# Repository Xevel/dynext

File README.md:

dynext
======

Dynamixel extension board.

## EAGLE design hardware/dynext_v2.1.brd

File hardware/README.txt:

Dynext - universal dynamixel device
===================================

V1.0 - 2014/03/02
- 4 layers
- first manufactured board
- smaller power section
- added voltage ref
- cleaner separation of different voltages, and corresponding return path

v0.2 - unfinished, was too hard to route in 2 layers. The power section was nice though.

v0.1 - unfinished, was too hard to route in 2 layers

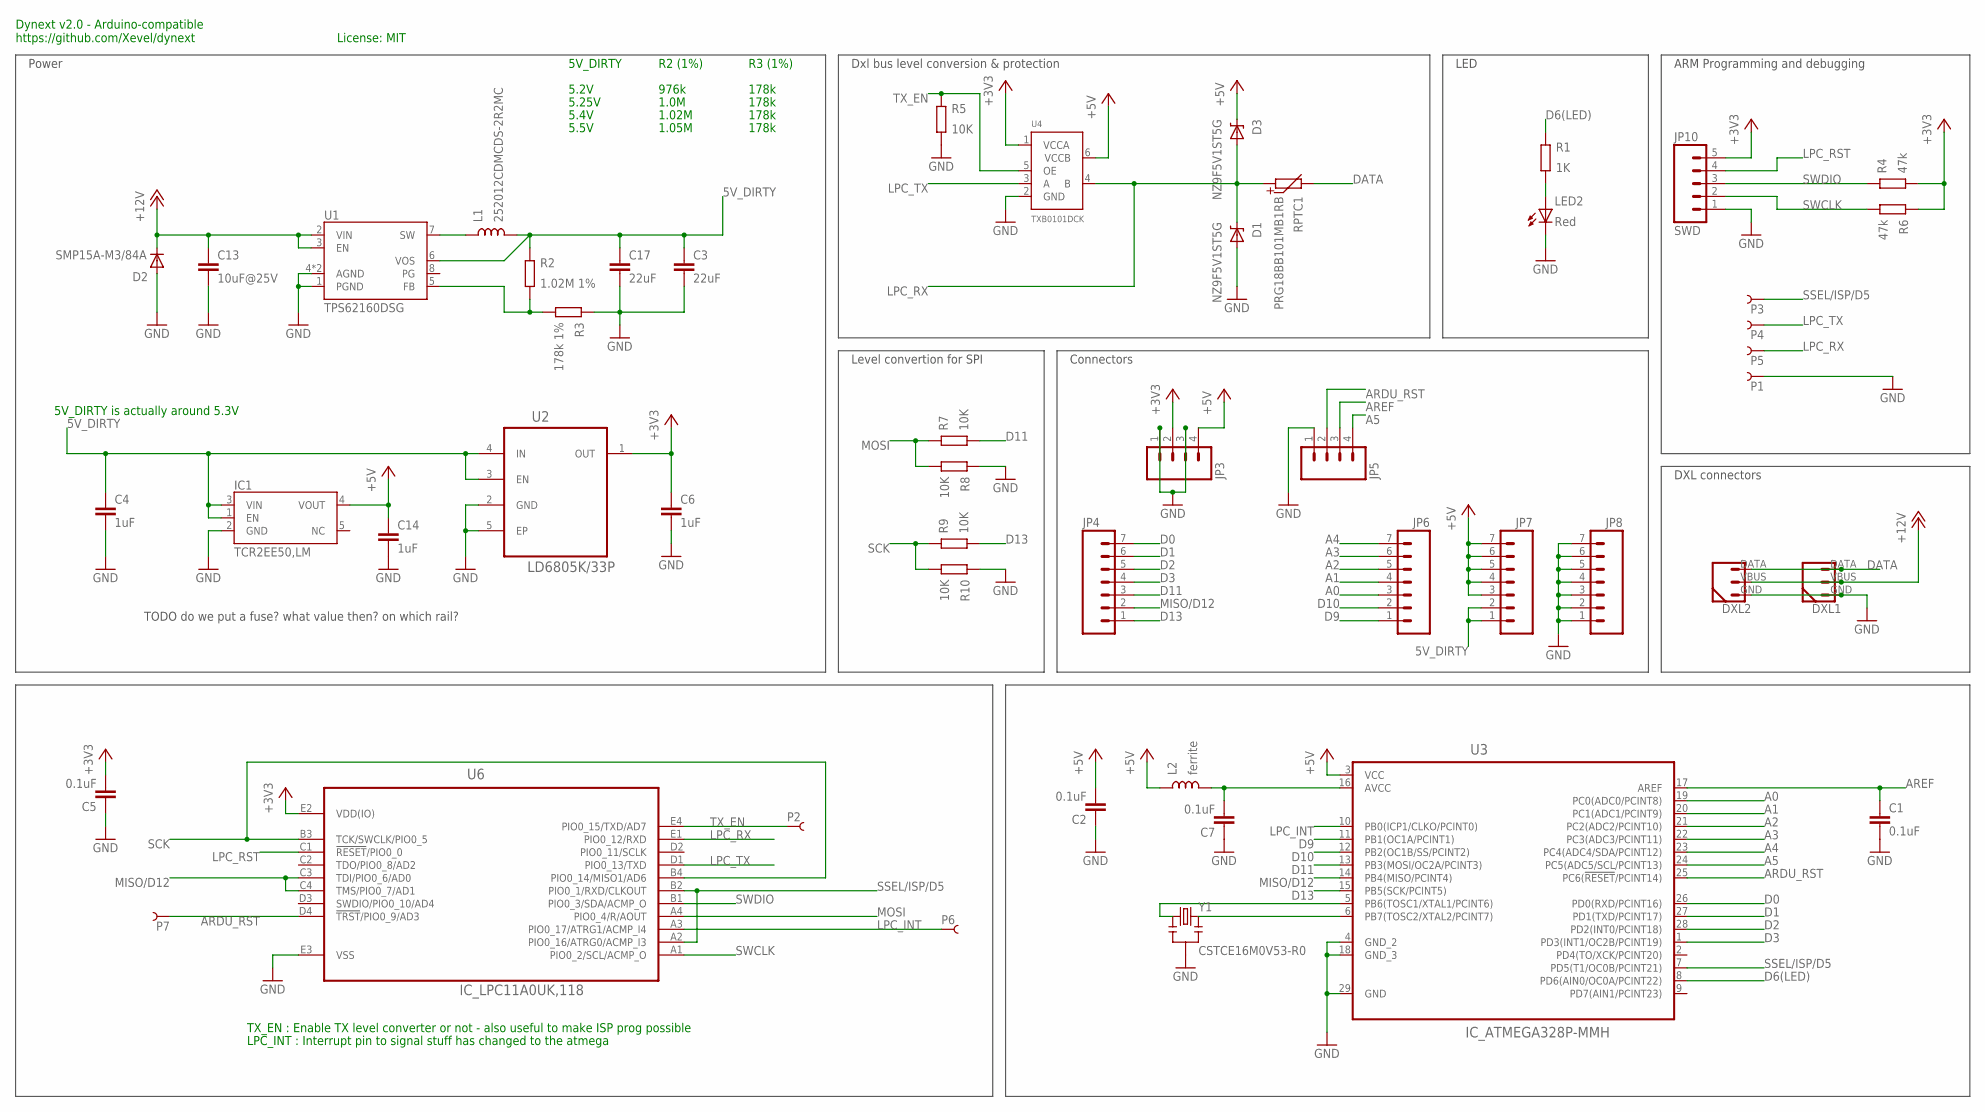
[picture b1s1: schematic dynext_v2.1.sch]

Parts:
C1, C2, C5, C7: 0.1uF; 0201_N
C3, C17: 22uF; 1206_N
C4, C6, C14: 1uF; 0402_N
C13: 10uF@25V; 0805_N
D1, D3: NZ9F5V1ST5G; SOD-923_N
D2: SMP15A-M3/84A; DO-220AA
DXL1, DXL2: DYNAMIXEL_3POS-R; DYNAMIXEL_3POS_RIGHT
IC1: TCR2EE50,LM; SOT50P160X60-5N
JP3, JP5: M041X04_NO_SILK; 1X04_NO_SILK
JP4, JP6, JP7: M07NO_SILK; 1X07_NO_SILK
JP8: M07SQUARE_ALL; 1X07_SQUARE_ALL
JP10: SWD; 1X05-1.27MM
L1: 252012CDMCDS-2R2MC; 1008_N
L2: ferrite; 0402_N
LED2: Red; D_0603_N
P1, P3, P4, P5: PIN_SMD_0.8X2
P2, P6, P7: PIN_SMD_1X1
R1: 1K; 0201_N
R2: 1.02M 1%; 0201_N
R3: 178k 1%; 0201_N
R4, R6: 47k; 0201_N
R5, R7, R8, R9, R10: 10K; 0201_N
RPTC1: PRG18BB101MB1RB; 0603_N
U1: TPS62160DSG; SON50P200X200X80-9L
U2: LD6805K/33P; NXP_LD6805
U3: IC_ATMEGA328P-MMH; QFN45P400X400X100-29N
U4: TXB0101DCK; SC70-6
U6: IC_LPC11A0UK,118; BGA20C50P_250X250X65
Y1: CSTCE16M0V53-R0; RESONATOR-SMD

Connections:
5V_DIRTY: C3.1, C4.1, C17.1, IC1.1 (EN), IC1.3 (VIN), JP7.1, JP7.2, L1.2, R2.2, U1.6 (VOS), U2.3 (EN), U2.4 (IN)
+3V3: C5.2, C6.1, JP3.2, JP10.5, R4.1, R6.2, U2.1 (OUT), U4.1 (VCCA), U6.E2 (VDD(IO))
+5V: C2.2, C14.1, D3.C, IC1.4 (VOUT), JP3.4, JP7.3, JP7.4, JP7.5, JP7.6, JP7.7, L2.1, U3.3 (VCC), U4.6 (VCCB)
+12V: C13.1, D2.C, DXL1.VBUS (2), DXL2.VBUS (2), U1.2 (VIN), U1.3 (EN)
A0: JP6.3, U3.19 (PC0(ADC0/PCINT8))
A1: JP6.4, U3.20 (PC1(ADC1/PCINT9))
A2: JP6.5, U3.21 (PC2(ADC2/PCINT10))
A3: JP6.6, U3.22 (PC3(ADC3/PCINT11))
A4: JP6.7, U3.23 (PC4(ADC4/SDA/PCINT12))
A5: JP5.4, U3.24 (PC5(ADC5/SCL/PCINT13))
ARDU_RST: JP5.2, P7.P$1, U3.25 (PC6(!RESET!/PCINT14)), U6.D4 (!TRST!/PIO0_9/AD3)
AREF: C1.1, JP5.3, U3.17 (AREF)
AVCC: C7.2, L2.2, U3.16 (AVCC)
D0: JP4.7, U3.26 (PD0(RXD/PCINT16))
D1: JP4.6, U3.27 (PD1(TXD/PCINT17))
D2: JP4.5, U3.28 (PD2(INT0/PCINT18))
D3: JP4.4, U3.1 (PD3(INT1/OC2B/PCINT19))
D6(LED): R1.2, U3.8 (PD6(AIN0/OC0A/PCINT22))
D9: JP6.1, U3.11 (PB1(OC1A/PCINT1))
D10: JP6.2, U3.12 (PB2(OC1B/SS/PCINT2))
D11: JP4.3, R7.1, U3.13 (PB3(MOSI/OC2A/PCINT3))
D13: JP4.1, R9.1, U3.15 (PB5(SCK/PCINT5))
DATA: DXL1.DATA (3), DXL2.DATA (3), RPTC1.2
GND: C1.2, C2.1, C3.2, C4.2, C5.1, C6.2, C7.1, C13.2, C14.2, C17.2, D1.A, D2.A, DXL1.GND (1), DXL2.GND (1), IC1.2 (GND), JP3.1, JP3.3, JP5.1, JP8.1, JP8.2, JP8.3, JP8.4, JP8.5, JP8.6, JP8.7, JP10.1, LED2.C, P1.PIN, R3.2, R5.1, R8.2, R10.2, U1.1 (PGND), U1.4 (AGND), U1.9 (AGND), U2.2 (GND), U2.5 (EP), U3.4 (GND_2), U3.18 (GND_3), U3.29 (GND), U4.2 (GND), U6.E3 (VSS), Y1.2
LPC_INT: P6.P$1, U3.10 (PB0(ICP1/CLKO/PCINT0)), U6.A3 (PIO0_17/ATRG1/ACMP_I4)
LPC_RST: JP10.4, U6.C1 (!RESET!/PIO0_0)
LPC_RX: D1.C, D3.A, P5.PIN, RPTC1.1, U4.4 (B), U6.E1 (PIO0_12/RXD)
LPC_TX: P4.PIN, U4.3 (A), U6.D1 (PIO0_13/TXD)
MISO/D12: JP4.2, U3.14 (PB4(MISO/PCINT4)), U6.C3 (TDI/PIO0_6/AD0), U6.C4 (TMS/PIO0_7/AD1)
MOSI: R7.2, R8.1, U6.A4 (PIO0_4/R/AOUT)
unnamed: L1.1, U1.7 (SW)
unnamed: LED2.A, R1.1
unnamed: U3.5 (PB6(TOSC1/XTAL1/PCINT6)), Y1.1
unnamed: U3.6 (PB7(TOSC2/XTAL2/PCINT7)), Y1.3
unnamed: R2.1, R3.1, U1.5 (FB)
SCK: R9.2, R10.1, U6.B3 (TCK/SWCLK/PIO0_5), U6.B4 (PIO0_14/MISO1/AD6)
SSEL/ISP/D5: P3.PIN, U3.7 (PD5(T1/OC0B/PCINT21)), U6.A2 (PIO0_16/ATRG0/ACMP_I3), U6.B2 (PIO0_1/RXD/CLKOUT)
SWCLK: JP10.2, R6.1, U6.A1 (PIO0_2/SCL/ACMP_O)
SWDIO: JP10.3, R4.2, U6.B1 (PIO0_3/SDA/ACMP_O)
TX_EN: P2.P$1, R5.2, U4.5 (OE), U6.E4 (PIO0_15/TXD/AD7)

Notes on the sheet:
DXL connectors
Power
ARM Programming and debugging
Dxl bus level conversion & protection
LED
Connectors
Dynext v2.0 - Arduino-compatible https://github.com/Xevel/dynext
License: MIT
LPC_INT : Interrupt pin to signal stuff has changed to the atmega
TX_EN : Enable TX level converter or not - also useful to make ISP prog possible
TODO do we put a fuse? what value then? on which rail?
Level convertion for SPI
5V_DIRTY is actually around 5.3V
R2 (1%)
R3 (1%)
5.2V
5.4V
5.25V
5.5V
976k
178k
1.0M
1.02M
1.05M
5V_DIRTY

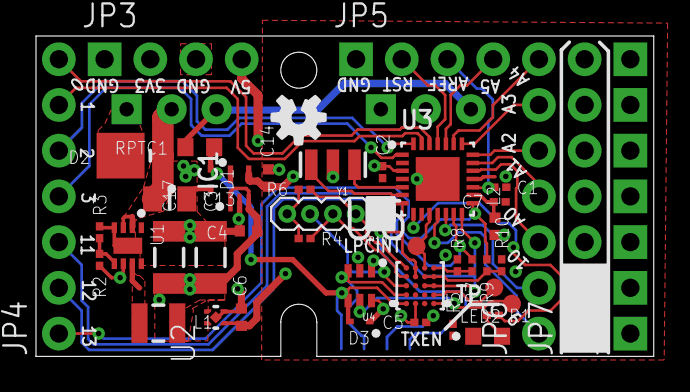
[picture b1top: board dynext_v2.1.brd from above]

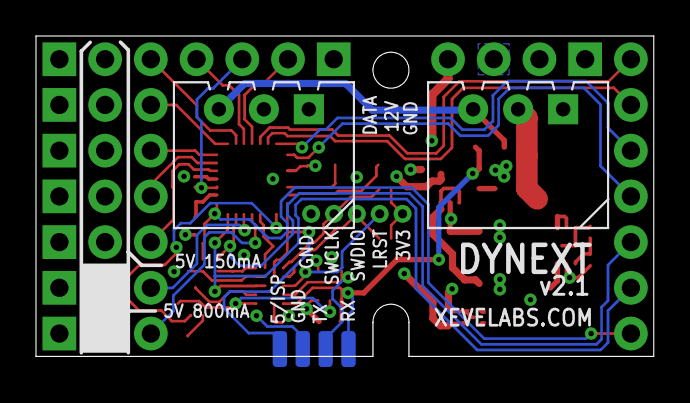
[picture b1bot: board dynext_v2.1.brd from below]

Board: 4 copper layers, 34.3 x 17.8 mm, 51 parts (6 on the bottom side), 40 nets.

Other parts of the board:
U$1: OSHW-LOGO-S

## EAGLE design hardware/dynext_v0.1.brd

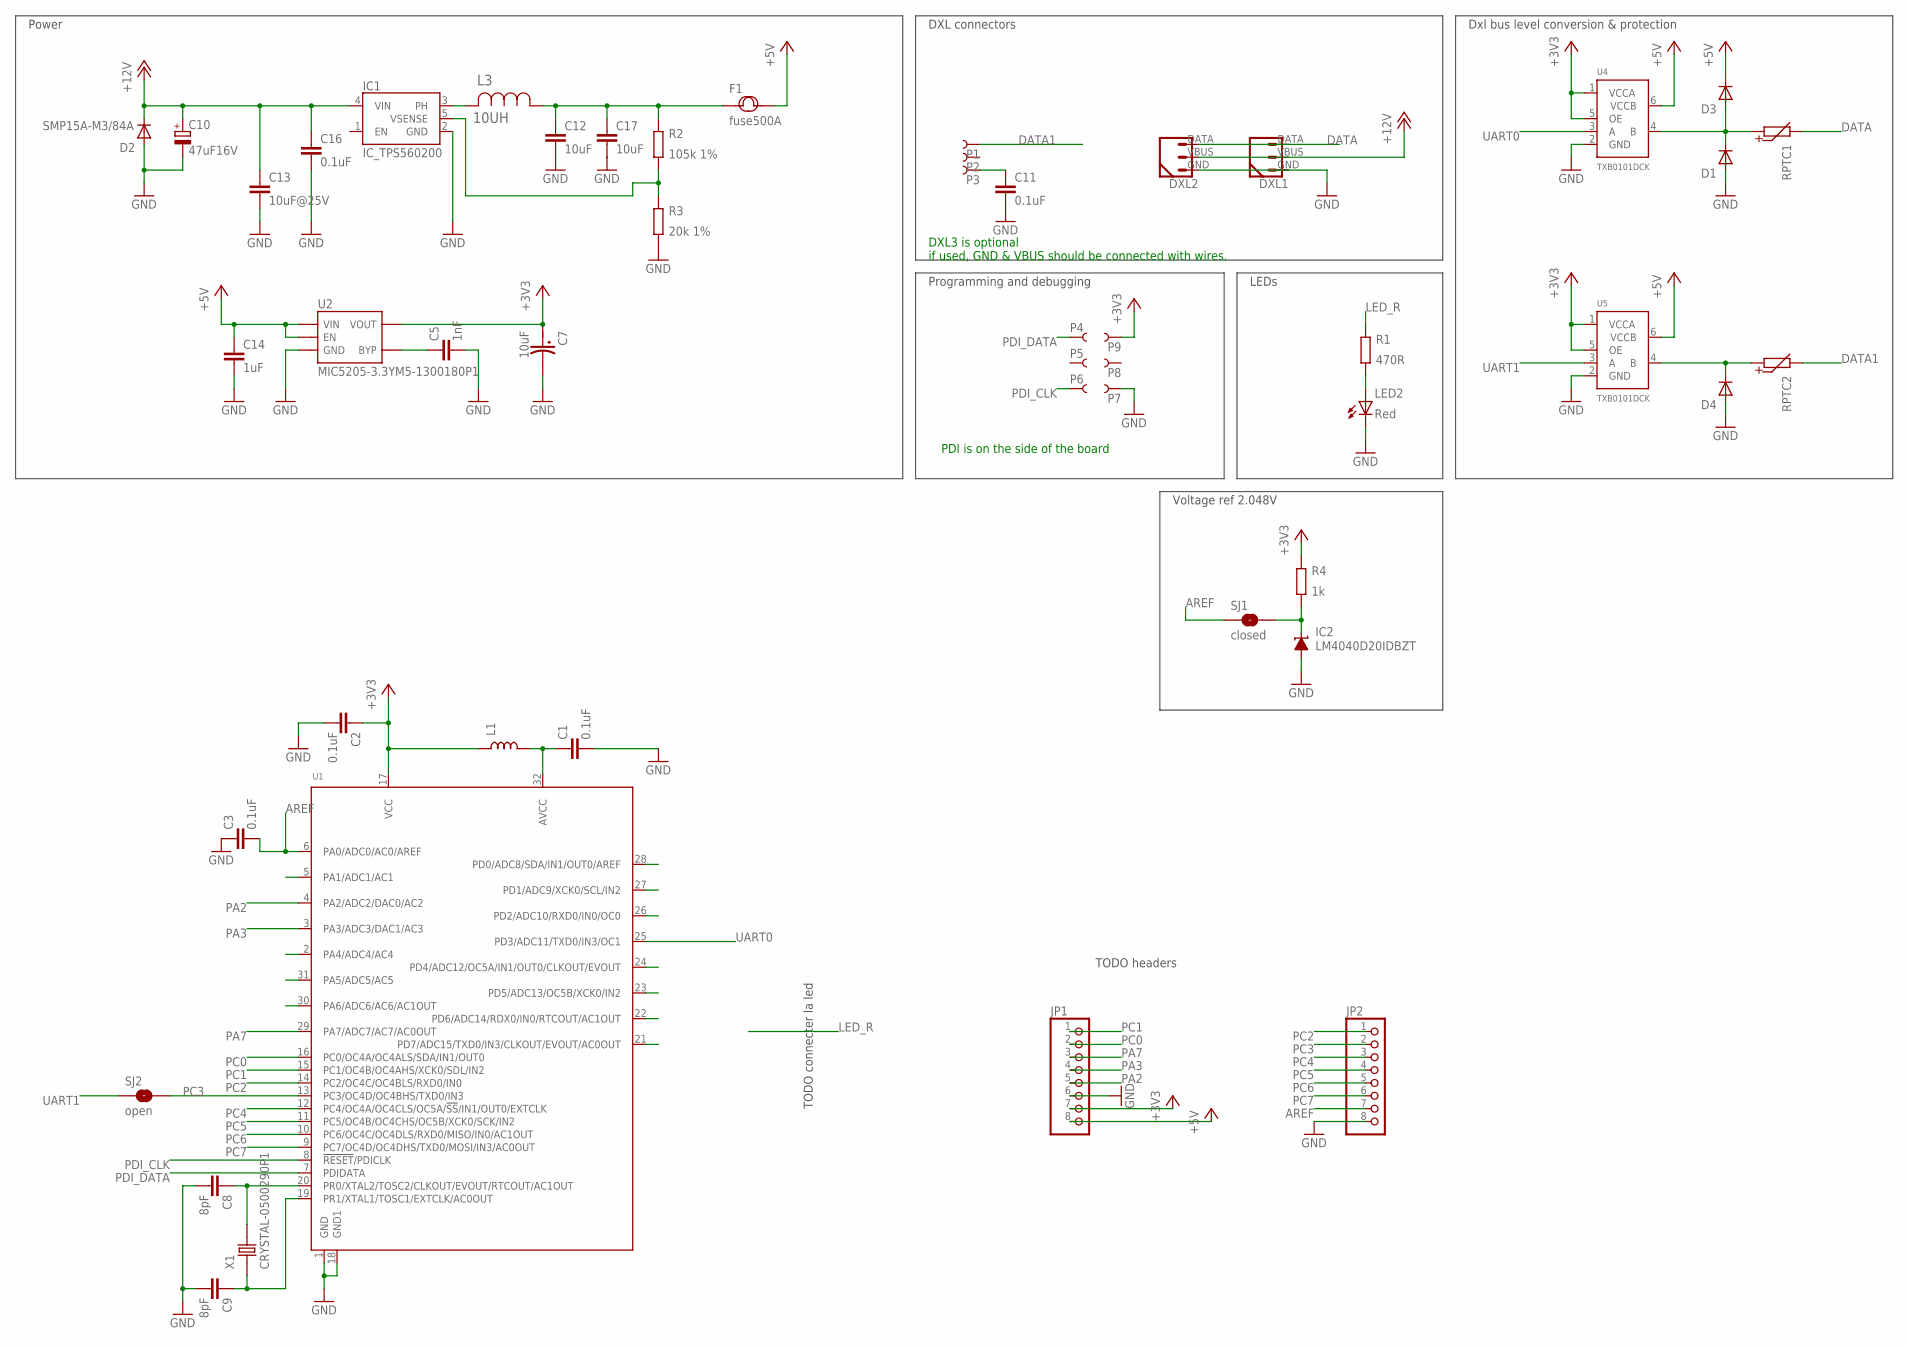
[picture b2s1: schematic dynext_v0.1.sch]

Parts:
C1, C2, C3, C11, C16: 0.1uF; 0402_N
C5: 1nF; 0402_N
C7: 10uF; AVX-A
C8, C9: 8pF; 0402_N
C10: 47uF16V; UD-5X5,8_NICHICON
C12, C17: 10uF; 0805_N
C13: 10uF@25V; 0805_N
C14: 1uF; 0402_N
D1, D3, D4: DIODE-SOD523; SOD-523_N
D2: SMP15A-M3/84A; DO-220AA
DXL1, DXL2: DYNAMIXEL_3POS-T; DYNAMIXEL_3POS_TOP
F1: fuse500A; F1206
IC1: IC_TPS560200; SOT-23-5_N
IC2: LM4040D20IDBZT; DBZ_R-PDSO-G3
JP1, JP2: PINHD-1X8R; 1X08_ROUND
L1: L0603; 0603_N
L3: 10UH; IND_ELL4XG
LED2: Red; D_0603_N
P1, P2, P3, P4, P6, P7, P9: PIN_SMD_2X2.5
P5, P8: PIN_SMD_1X1
R1: 470R; 0402_N
R2: 105k 1%; 0402_N
R3: 20k 1%; 0402_N
R4: 1k; 0402_N
RPTC1, RPTC2: R-PTC0603; 0603_N
SJ1: closed; SJ_2S-TRACE2
SJ2: open; SJ_2S-NO
U1: ATXMEGAE5-MU_MOD; QFN-32_50P_L_MOD
U2: MIC5205-3.3YM5-1300180P1; SOT23-5
U4, U5: TXB0101DCK; SC70-6
X1: CRYSTAL-0500290P1; 2P-SMD-5.0X3.2

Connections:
+3V3: C2.1, C7.+ (1), JP1.7, L1.1, P9.PIN, R4.2, U1.17 (VCC), U2.5 (VOUT), U4.1 (VCCA), U4.5 (OE), U5.1 (VCCA), U5.5 (OE)
+5V: C14.1, D3.C, F1.2, JP1.8, U2.1 (VIN), U2.3 (EN), U4.6 (VCCB), U5.6 (VCCB)
+12V: C10.+, C13.1, C16.1, D2.C, DXL1.VBUS (2), DXL2.VBUS (2), IC1.4 (VIN)
AREF: C3.2, JP2.7, SJ1.1, U1.6 (PA0/ADC0/AC0/AREF)
DATA: DXL1.DATA (3), DXL2.DATA (3), RPTC1.2
DATA1: P1.PIN, RPTC2.2
GND: C1.2, C2.2, C3.1, C5.2, C7.- (2), C8.2, C9.2, C10.-, C11.2, C12.2, C13.2, C14.2, C16.2, C17.2, D1.A, D2.A, D4.A, DXL1.GND (1), DXL2.GND (1), IC1.2 (GND), IC2.2 (A), JP1.6, JP2.8, LED2.C, P7.PIN, R3.1, U1.1 (GND), U1.18 (GND1), U2.2 (GND), U4.2 (GND), U5.2 (GND)
LED_R: R1.2
unnamed: C11.1, P3.PIN
unnamed: C1.1, L1.2, U1.32 (AVCC)
unnamed: LED2.A, R1.1
unnamed: C8.1, U1.20 (PR0/XTAL2/TOSC2/CLKOUT/EVOUT/RTCOUT/AC1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), X1.2
unnamed: C5.1, U2.4 (BYP)
unnamed: C9.1, U1.19 (PR1/XTAL1/TOSC1/EXTCLK/AC0OUT), X1.1
unnamed: D1.C, D3.A, RPTC1.1, U4.4 (B)
unnamed: D4.C, RPTC2.1, U5.4 (B)
unnamed: C12.1, C17.1, F1.1, L3.1, R2.2
unnamed: IC1.5 (VSENSE), R2.1, R3.2
unnamed: IC2.1 (C), R4.1, SJ1.2
PA2: JP1.5, U1.4 (PA2/ADC2/DAC0/AC2)
PA3: JP1.4, U1.3 (PA3/ADC3/DAC1/AC3)
PA7: JP1.3, U1.29 (PA7/ADC7/AC7/AC0OUT)
PC0: JP1.2, U1.16 (PC0/OC4A/OC4ALS/SDA/IN1/OUT0)
PC1: JP1.1, U1.15 (PC1/OC4B/OC4AHS/XCK0/SDL/IN2)
PC2: JP2.1, U1.14 (PC2/OC4C/OC4BLS/RXD0/IN0)
PC3: JP2.2, SJ2.2, U1.13 (PC3/OC4D/OC4BHS/TXD0/IN3)
PC4: JP2.3, U1.12 (PC4/OC4A/OC4CLS/OC5A/!SS!/IN1/OUT0/EXTC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)
PC5: JP2.4, U1.11 (PC5/OC4B/OC4CHS/OC5B/XCK0/SCK/IN2)
PC6: JP2.5, U1.10 (PC6/OC4C/OC4DLS/RXD0/MISO/IN0/AC1OUT)
PC7: JP2.6, U1.9 (PC7/OC4D/OC4DHS/TXD0/MOSI/IN3/AC0OUT)
PDI_CLK: P6.PIN, U1.8 (!RESET!/PDICLK)
PDI_DATA: P4.PIN, U1.7 (PDIDATA)
PH_L: IC1.3 (PH), L3.2
UART0: U1.25 (PD3/ADC11/TXD0/IN3/OC1), U4.3 (A)
UART1: SJ2.1, U5.3 (A)

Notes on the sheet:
DXL connectors
Power
PDI is on the side of the board
Programming and debugging
Dxl bus level conversion & protection
LEDs
DXL3 is optional if used, GND & VBUS should be connected with wires.
Voltage ref 2.048V
TODO connecter la led
TODO headers

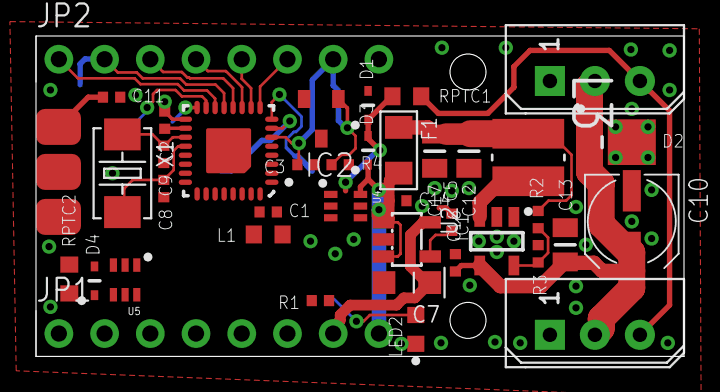
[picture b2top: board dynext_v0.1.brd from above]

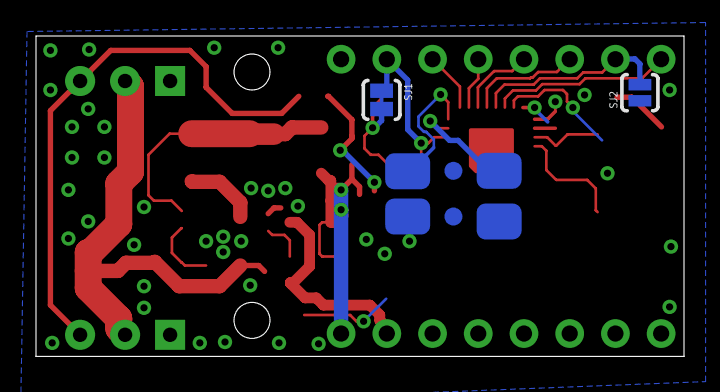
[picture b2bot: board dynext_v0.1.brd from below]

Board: 2 copper layers, 36.0 x 17.8 mm, 50 parts (8 on the bottom side), 34 nets.

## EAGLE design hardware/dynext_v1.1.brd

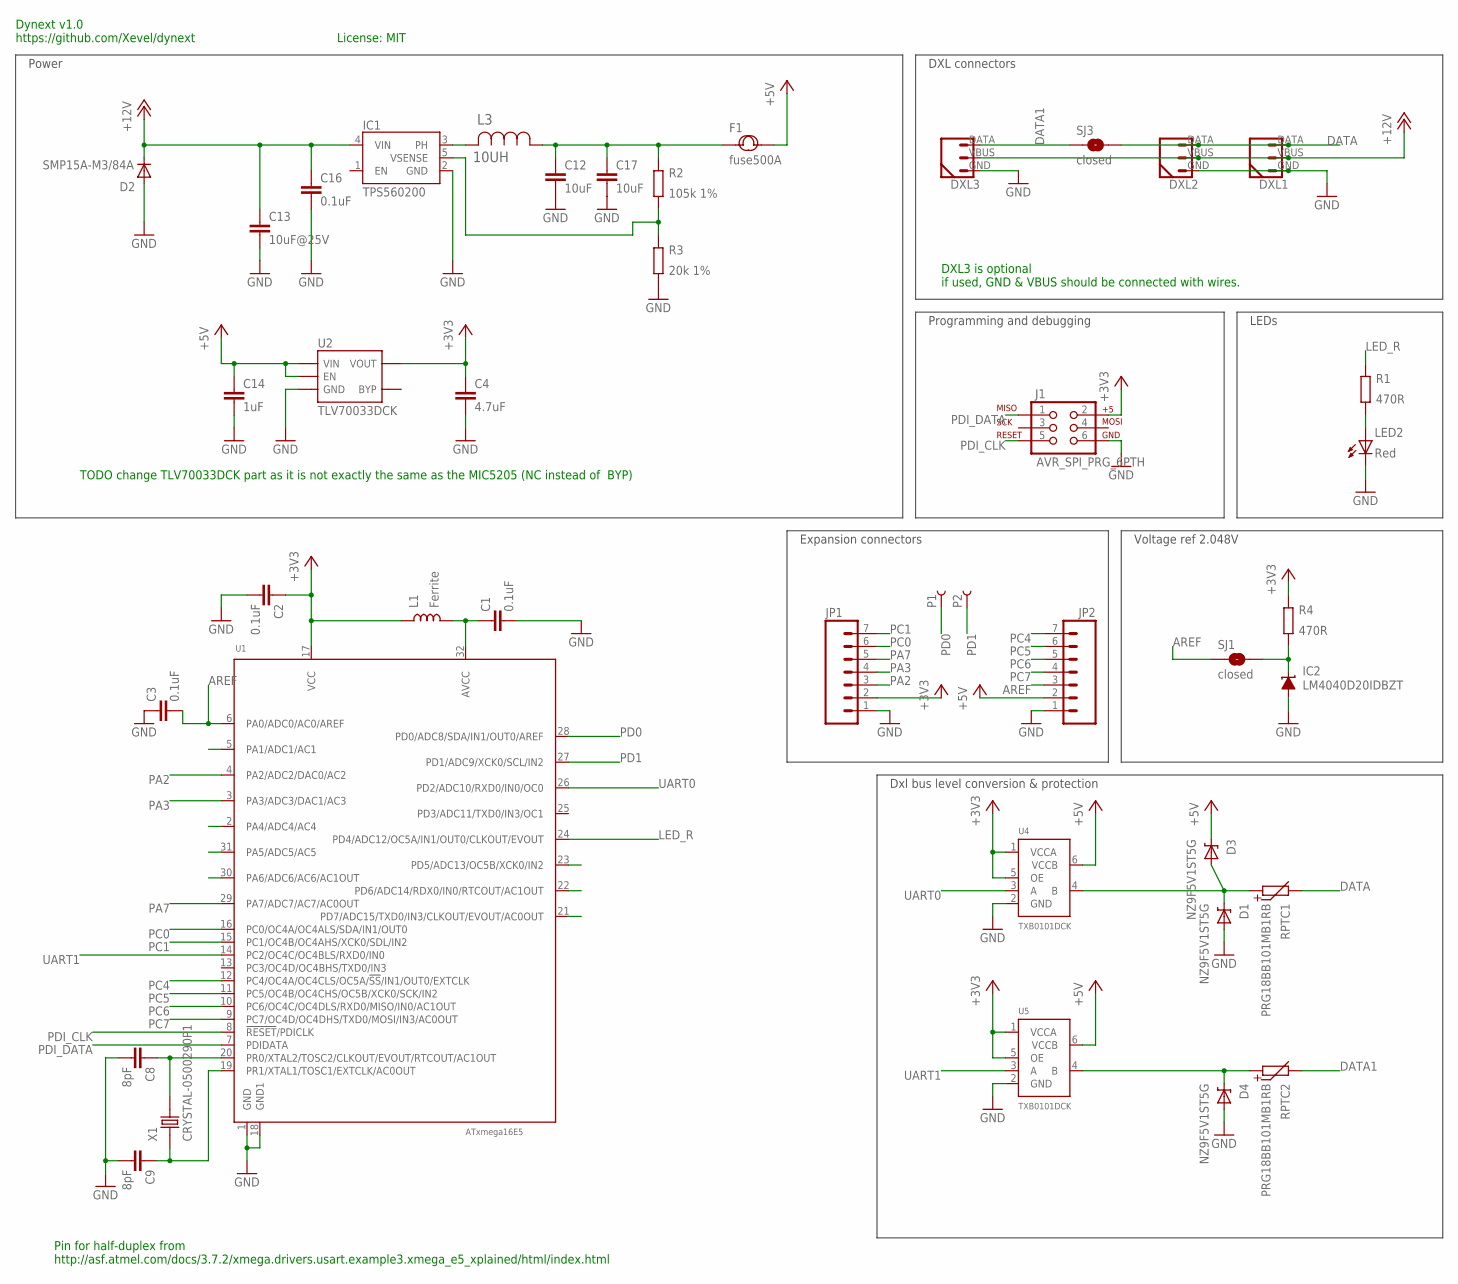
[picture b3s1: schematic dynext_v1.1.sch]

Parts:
C1, C2, C3, C16: 0.1uF; 0402_N
C4: 4.7uF; 0603_N
C8, C9: 8pF; 0402_N
C12, C17: 10uF; 0805_N
C13: 10uF@25V; 0805_N
C14: 1uF; 0402_N
D1, D3, D4: NZ9F5V1ST5G; SOD-923_N
D2: SMP15A-M3/84A; DO-220AA
DXL1, DXL2: DYNAMIXEL_3POS-T; DYNAMIXEL_3POS_TOP
DXL3: DYNAMIXEL_3POS-R; DYNAMIXEL_3POS_RIGHT
F1: fuse500A; F1206
IC1: TPS560200; SOT-23-5_N
IC2: LM4040D20IDBZT; DBZ_R-PDSO-G3
J1: AVR_SPI_PRG_6PTH; 2X3
JP1, JP2: M07; 1X07
L1: Ferrite; 0603_N
L3: 10UH; IND_ELL4XG
LED2: Red; D_0603_N
P1, P2: PIN_SMD_2X2.5
R1, R4: 470R; 0402_N
R2: 105k 1%; 0402_N
R3: 20k 1%; 0402_N
RPTC1, RPTC2: PRG18BB101MB1RB; 0603_N
SJ1, SJ3: closed; SJ_2S-TRACE2
U1: ATxmega16E5; QFN-32_50P_L_MOD
U2: TLV70033DCK; SC70-5
U4, U5: TXB0101DCK; SC70-6
X1: CRYSTAL-0500290P1; 2P-SMD-5.0X3.2

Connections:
+3V3: C2.1, C4.1, J1.2, JP1.2, L1.1, R4.2, U1.17 (VCC), U2.5 (VOUT), U4.1 (VCCA), U4.5 (OE), U5.1 (VCCA), U5.5 (OE)
+5V: C14.1, D3.C, F1.2, JP2.2, U2.1 (VIN), U2.3 (EN), U4.6 (VCCB), U5.6 (VCCB)
+12V: C13.1, C16.1, D2.C, DXL1.VBUS (2), DXL2.VBUS (2), DXL3.VBUS (2), IC1.4 (VIN)
AREF: C3.2, JP2.3, SJ1.1, U1.6 (PA0/ADC0/AC0/AREF)
DATA: DXL1.DATA (3), DXL2.DATA (3), RPTC1.2, SJ3.2
DATA1: DXL3.DATA (3), RPTC2.2, SJ3.1
GND: C1.2, C2.2, C3.1, C4.2, C8.2, C9.2, C12.2, C13.2, C14.2, C16.2, C17.2, D1.A, D2.A, D4.A, DXL1.GND (1), DXL2.GND (1), DXL3.GND (1), IC1.2 (GND), IC2.2 (A), J1.6, JP1.1, JP2.1, LED2.C, R3.1, U1.1 (GND), U1.18 (GND1), U2.2 (GND), U4.2 (GND), U5.2 (GND)
LED_R: R1.2, U1.24 (PD4/ADC12/OC5A/IN1/OUT0/CLKOUT/EVOUT)
unnamed: C1.1, L1.2, U1.32 (AVCC)
unnamed: LED2.A, R1.1
unnamed: C8.1, U1.20 (PR0/XTAL2/TOSC2/CLKOUT/EVOUT/RTCOUT/AC1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), X1.2
unnamed: C9.1, U1.19 (PR1/XTAL1/TOSC1/EXTCLK/AC0OUT), X1.1
unnamed: D1.C, D3.A, RPTC1.1, U4.4 (B)
unnamed: D4.C, RPTC2.1, U5.4 (B)
unnamed: C12.1, C17.1, F1.1, L3.1, R2.2
unnamed: IC1.5 (VSENSE), R2.1, R3.2
unnamed: IC2.1 (C), R4.1, SJ1.2
PA2: JP1.3, U1.4 (PA2/ADC2/DAC0/AC2)
PA3: JP1.4, U1.3 (PA3/ADC3/DAC1/AC3)
PA7: JP1.5, U1.29 (PA7/ADC7/AC7/AC0OUT)
PC0: JP1.6, U1.16 (PC0/OC4A/OC4ALS/SDA/IN1/OUT0)
PC1: JP1.7, U1.15 (PC1/OC4B/OC4AHS/XCK0/SDL/IN2)
PC4: JP2.7, U1.12 (PC4/OC4A/OC4CLS/OC5A/!SS!/IN1/OUT0/EXTC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)
PC5: JP2.6, U1.11 (PC5/OC4B/OC4CHS/OC5B/XCK0/SCK/IN2)
PC6: JP2.5, U1.10 (PC6/OC4C/OC4DLS/RXD0/MISO/IN0/AC1OUT)
PC7: JP2.4, U1.9 (PC7/OC4D/OC4DHS/TXD0/MOSI/IN3/AC0OUT)
PD0: P1.PIN, U1.28 (PD0/ADC8/SDA/IN1/OUT0/AREF)
PD1: P2.PIN, U1.27 (PD1/ADC9/XCK0/SCL/IN2)
PDI_CLK: J1.5, U1.8 (!RESET!/PDICLK)
PDI_DATA: J1.1, U1.7 (PDIDATA)
PH_L: IC1.3 (PH), L3.2
UART0: U1.26 (PD2/ADC10/RXD0/IN0/OC0), U4.3 (A)
UART1: U1.14 (PC2/OC4C/OC4BLS/RXD0/IN0), U5.3 (A)

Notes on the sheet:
DXL connectors
Power
Programming and debugging
Dxl bus level conversion & protection
LEDs
DXL3 is optional if used, GND & VBUS should be connected with wires.
Voltage ref 2.048V
TODO change TLV70033DCK part as it is not exactly the same as the MIC5205 (NC instead of BYP)
Pin for half-duplex from http://asf.atmel.com/docs/3.7.2/xmega.drivers.usart.example3.xmega_e5_xplained/html/index.html
Expansion connectors
Dynext v1.0 https://github.com/Xevel/dynext
License: MIT

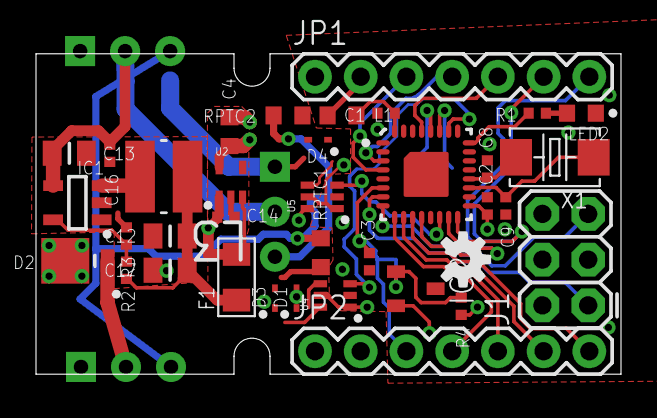
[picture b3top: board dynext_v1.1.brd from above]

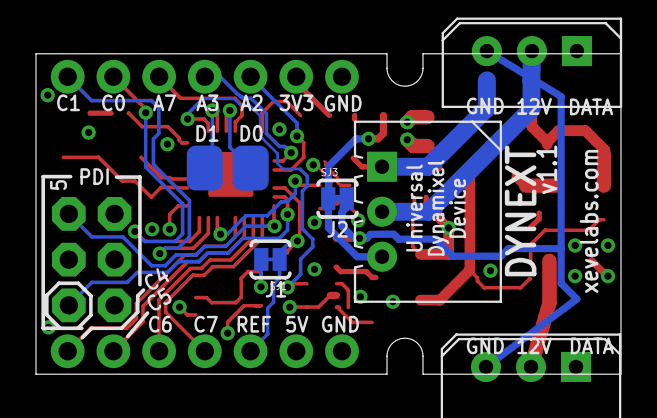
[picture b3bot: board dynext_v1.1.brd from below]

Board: 4 copper layers, 32.5 x 17.8 mm, 43 parts (5 on the bottom side), 33 nets.

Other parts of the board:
U$1: OSHW-LOGO-S

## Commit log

2014-03-04 Import of the eagle files
2014-03-04 Added all the readmes
2014-03-04 Added license on schematics
2014-03-04 Created empty Atmel Studio project
2014-03-06 Updated MCU footprint to avoid shitty manufacturing mistakes at board houses that remove polygones that have lines too small for their liking -_-
2014-03-28 New Dynext architecture with Cortex-M0 + Arduino-compatible ATmega328p. WIP
2014-03-28 Cleanup of versions of the board. Added semi-corrected version of v1, it I ever want to go back to it...
2014-03-29 Shifting things around, preparing for the real pinout & layout.
2014-03-30 Schematics stabilized, routing in half-way done.
2014-03-30 Routing is getting close to something viable. I probably will rip up some of the most complex parts to simplifiy them ><
2014-03-30 Routing roughly done and seems OK. More verif and silkscreen still needed.
2014-03-30 Added all the silkscreen. Potentially ready.
2014-03-31 Added some more silkscreen indications
2014-03-31 Rearrangement of the schematics for better fitting on the screen
2014-03-31 Some final minor tweaks. Board ordered.
2014-04-01 Updated schematics with final values for the switch reg voltage divider.
2014-04-01 Cosmetic details
2014-04-13 beginingh of the V2.1 of the board created, with little corrections (missing connection, missing pull-down resistor). Not complete or routed yet.

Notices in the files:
parts and their libraries:
SparkFun-Connectors: Licensing: CC v3.0 Share-Alike You are welcome to use this library for commercial purposes.
